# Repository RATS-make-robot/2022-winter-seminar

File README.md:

# 2022-winter-seminar
2022 겨울방학 재학생 세미나

1. 3D 모델링 + 3D 프린터
2. Git/Github (by [BEMELON](https://github.com/BEMELON))
3. OpenCV
4. KiCAD+PCB (by [js4ngu](https://github.com/js4ngu))
5. 시스템파워 설계

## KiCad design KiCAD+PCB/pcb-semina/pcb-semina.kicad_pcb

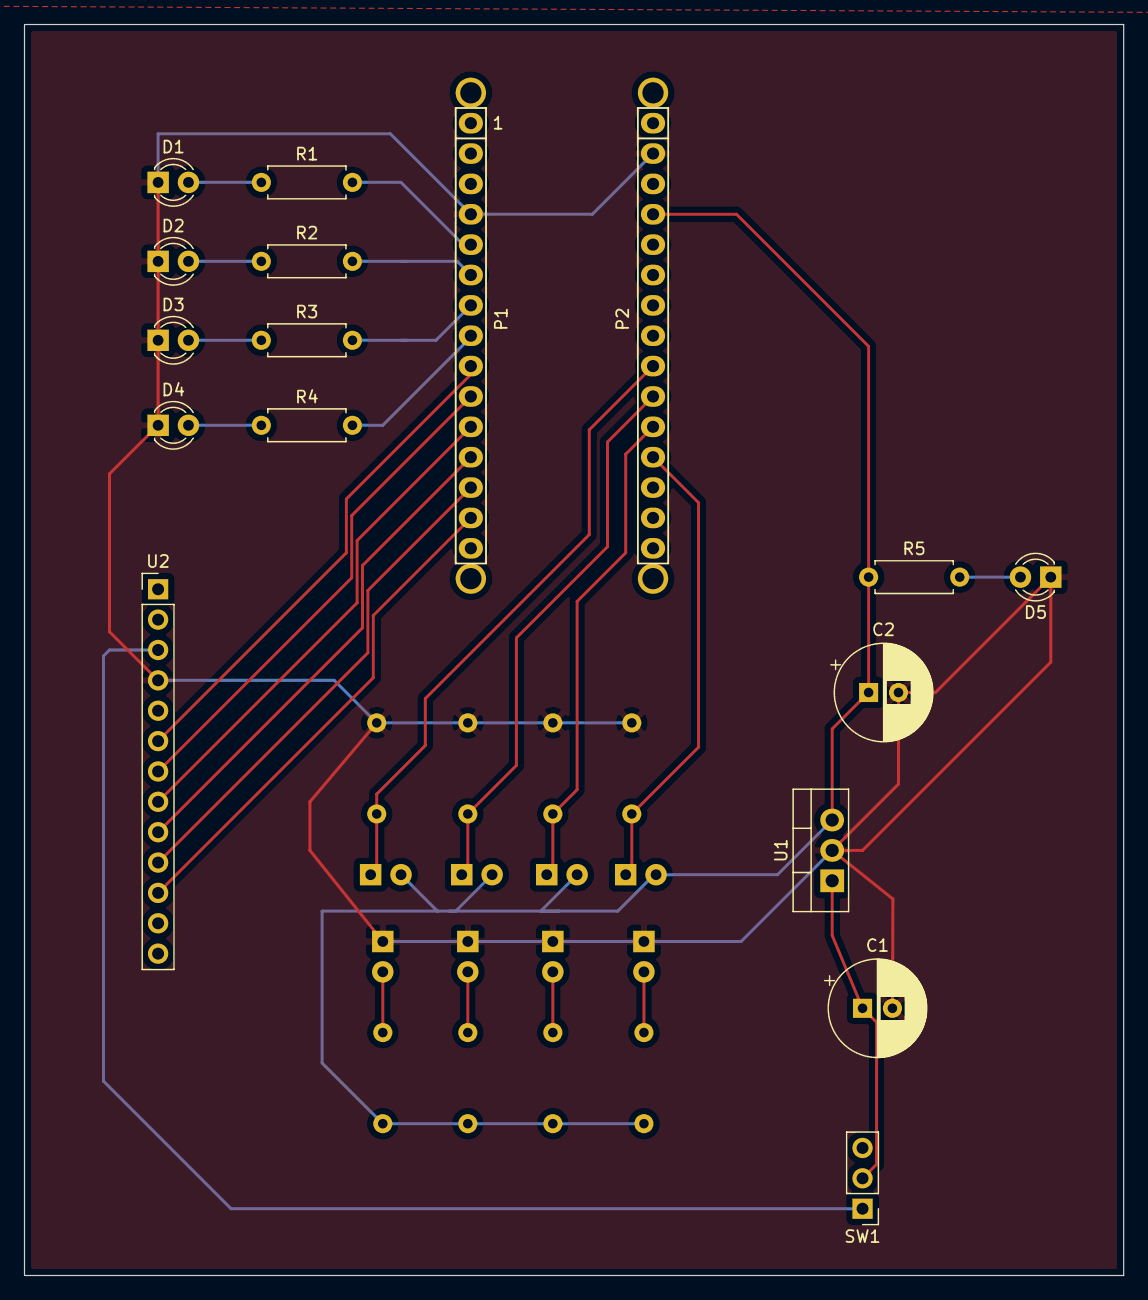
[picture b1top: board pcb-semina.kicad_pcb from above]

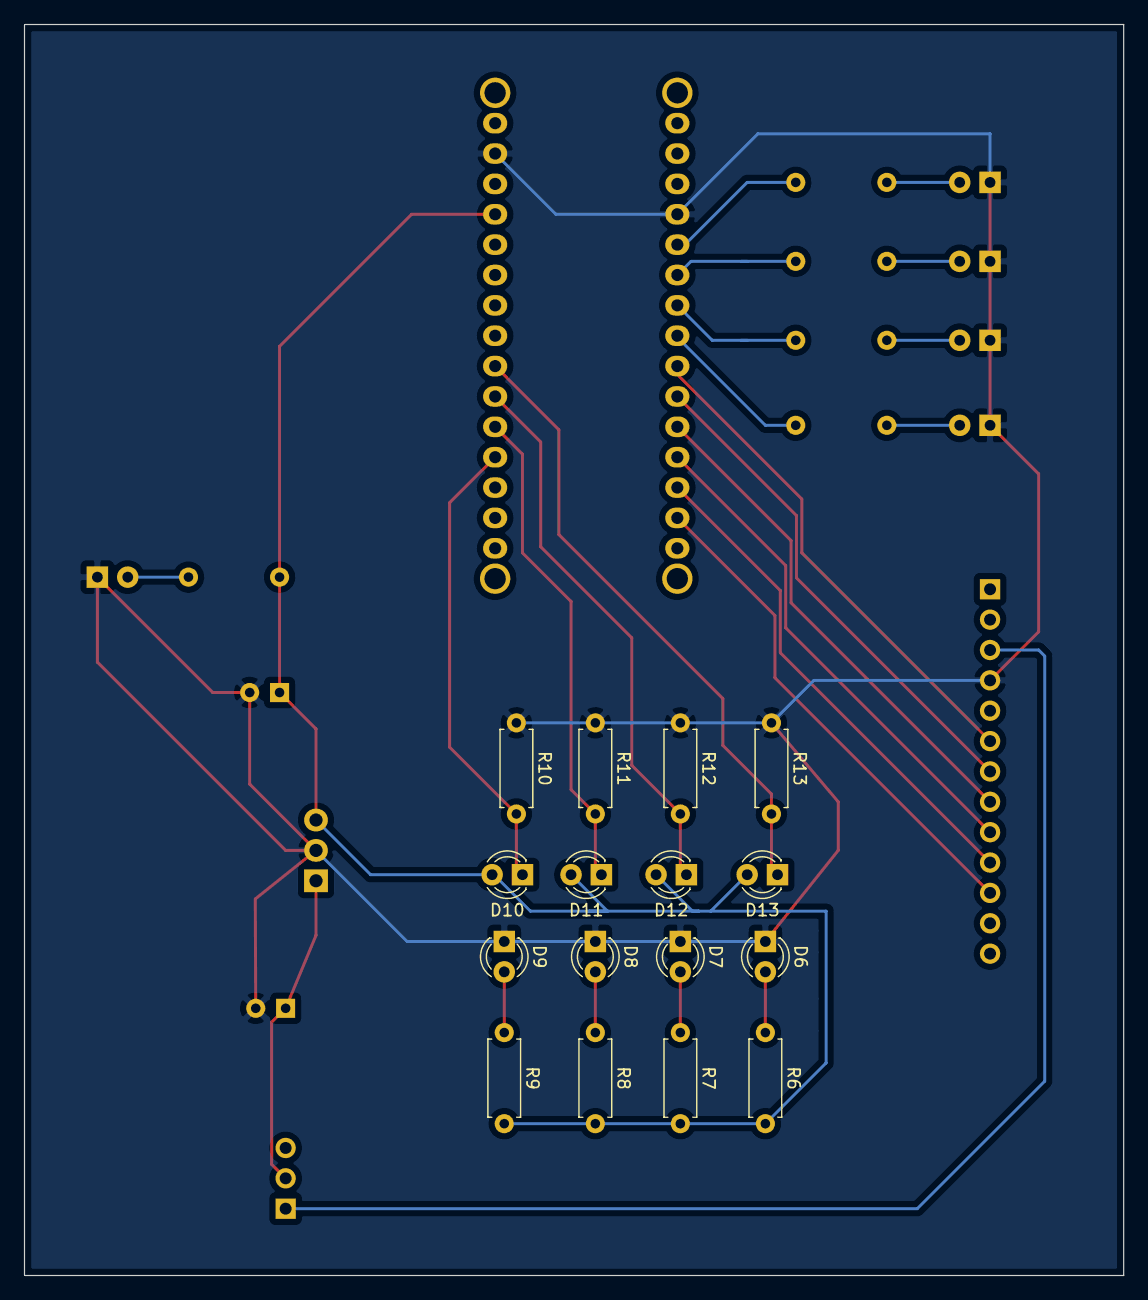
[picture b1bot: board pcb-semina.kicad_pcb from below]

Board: 2 copper layers, 91.9 x 104.6 mm, 37 parts (16 on the bottom side), 28 nets.

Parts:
C1: 0.33uF; CP_Radial_D8.0mm_P2.50mm
C2: 0.1uF; CP_Radial_D8.0mm_P2.50mm
D1, D2, D3, D4, D5: LED; LED_D3.0mm
D6, D7, D8, D9: EL-71; LED_D3.0mm
D10, D11, D12, D13: ST_7L; LED_D3.0mm
P1: Digital; Socket_Strip_Arduino_1x15
P2: Analog; Socket_Strip_Arduino_1x15
P3, P4, P5, P6: CONN_01X01; 1pin_Nano
R1, R2, R3, R4: 300; R_Axial_DIN0207_L6.3mm_D2.5mm_P7.62mm_Horizontal
R5: 330; R_Axial_DIN0207_L6.3mm_D2.5mm_P7.62mm_Horizontal
R6, R7, R8, R9: 100; R_Axial_DIN0207_L6.3mm_D2.5mm_P7.62mm_Horizontal
R10, R11, R12, R13: 1k; R_Axial_DIN0207_L6.3mm_D2.5mm_P7.62mm_Horizontal
SW1: SW_DIP_x01; PinHeader_1x03_P2.54mm_Vertical
U1: LM7805_TO220; TO-220-3_Vertical
U2: L298N; PinHeader_1x13_P2.54mm_Vertical

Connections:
+5V: C2.1, D10.2, D11.2, D12.2, D13.2, P2.4, R5.1, R6.2, R7.2, R8.2, R9.2, U1.3
+BATT: SW1.1, U2.3
/ADC0: D10.1, P2.12, R10.2
/ADC1: D11.1, P2.11, R11.2
/ADC2: D12.1, P2.10, R12.2
/ADC3: D13.1, P2.9, R13.2
/DIR0_L: P1.10, U2.7
/DIR0_R: P1.12, U2.9
/DIR1_L: P1.11, U2.8
/DIR1_R: P1.13, U2.10
/LED0: P1.5, R1.2
/LED1: P1.6, R2.2
/LED2: P1.7, R3.2
/LED3: P1.8, R4.2
/PWM_L: P1.9, U2.6
/PWM_R: P1.14, U2.11
/Reset: P1.3, P2.3
GND: C1.2, C2.2, D1.1, D2.1, D3.1, D4.1, D5.1, D6.1, D7.1, D8.1, D9.1, P1.4, P2.2, R10.1, R11.1, R12.1, R13.1, U1.2, U2.4
unnamed: C1.1, SW1.2, U1.1
unnamed: D1.2, R1.1
unnamed: D2.2, R2.1
unnamed: D3.2, R3.1
unnamed: D4.2, R4.1
unnamed: D5.2, R5.2
unnamed: D6.2, R6.1
unnamed: D7.2, R7.1
unnamed: D8.2, R8.1
unnamed: D9.2, R9.1

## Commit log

2022-02-05 KiCAD+PCB 강의자료
2022-02-10 Git/Github 세미나 강연자료
2022-02-12 자료 업데이트
